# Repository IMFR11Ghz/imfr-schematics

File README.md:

# imfr-schematics
imfr-schematics

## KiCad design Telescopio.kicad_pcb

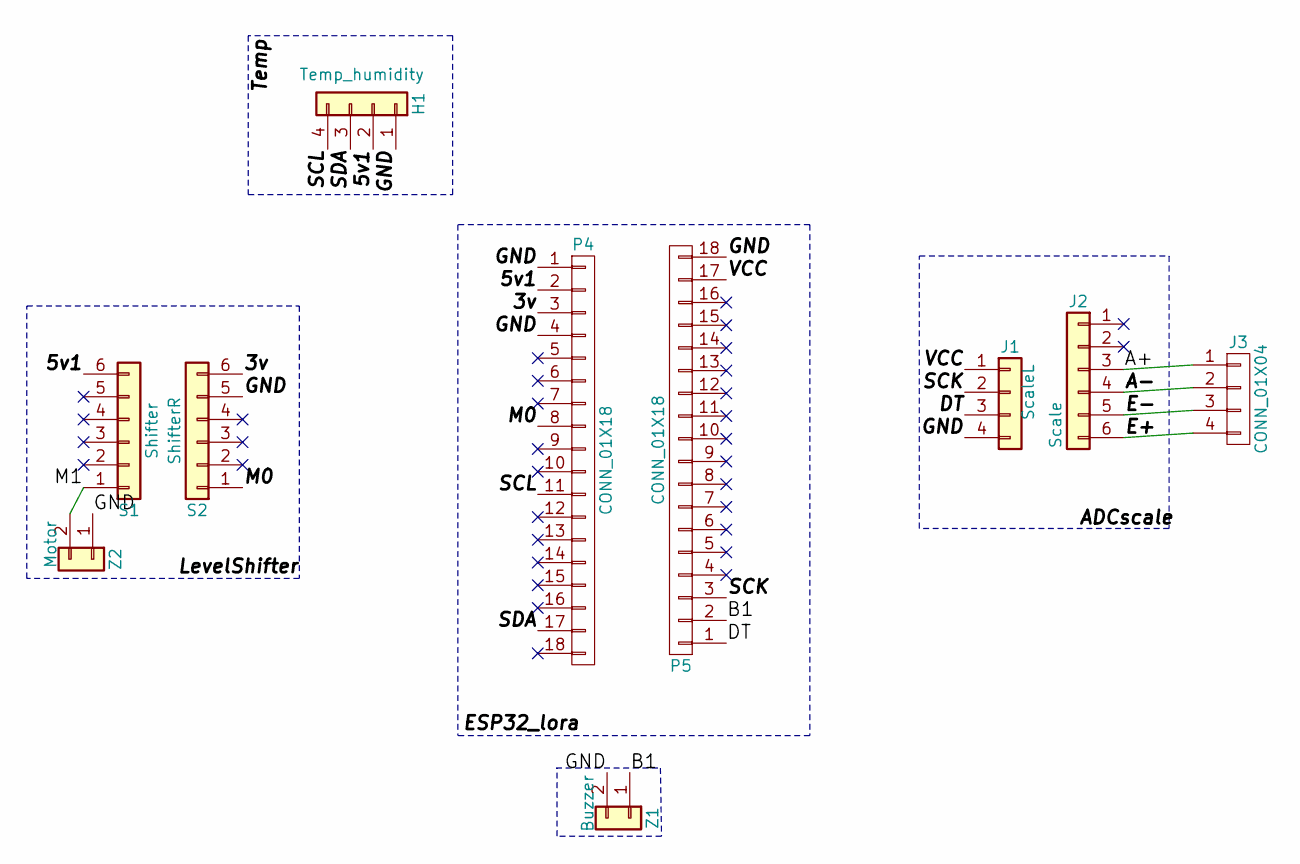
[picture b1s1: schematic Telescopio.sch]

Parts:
H1: Temp_humidity; Pin_Header_Straight_1x04_Pitch2.00mm
J1: ScaleL; Pin_Header_Straight_1x04
J2: Scale; Pin_Header_Straight_1x06
J3: CONN_01X04; Pin_Header_Straight_1x04_Pitch2.00mm
P4, P5: CONN_01X18; Pin_Header_Straight_1x18
S1: Shifter; Pin_Header_Straight_1x06
S2: ShifterR; Pin_Header_Straight_1x06
Z1: Buzzer; Pin_Header_Straight_1x02
Z2: Motor; Pin_Header_Straight_1x02

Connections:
/3v: P4.3, S2.6
/5v1: H1.2, P4.2, S1.6
/A+: J2.3, J3.1
/A-: J2.4, J3.2
/B1: P5.2, Z1.1
/DT: J1.3, P5.1
/E+: J2.6, J3.4
/E-: J2.5, J3.3
/GND: H1.1, J1.4, P4.1, P4.4, P5.18, S2.5, Z1.2, Z2.1
/M0: P4.8, S2.1
/M1: S1.1, Z2.2
/SCK: J1.2, P5.3
/SCL: H1.4, P4.11
/SDA: H1.3, P4.17
/VCC: J1.1, P5.17

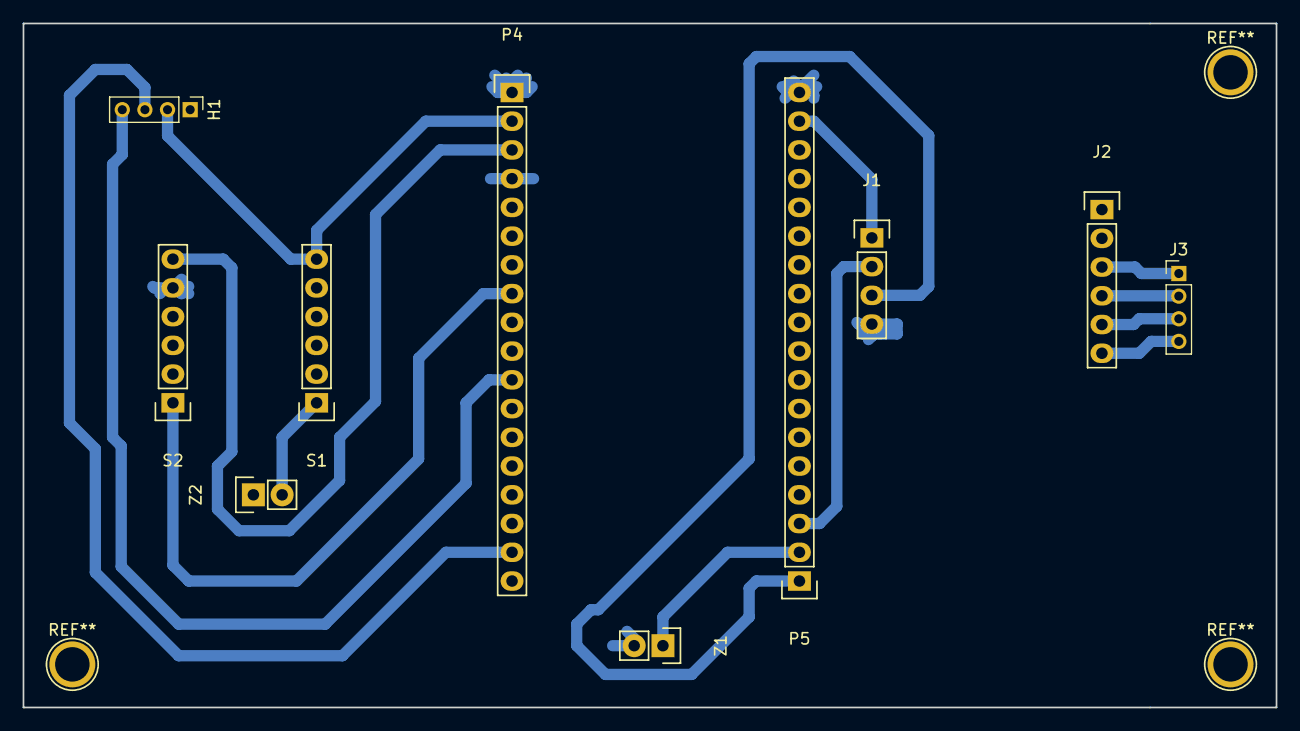
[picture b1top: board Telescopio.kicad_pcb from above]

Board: 2 copper layers, 110.7 x 60.5 mm, 10 parts (0 on the bottom side), 15 nets.

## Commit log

2017-06-16 initial commit repo Kicad
2017-06-16 print board
2017-06-16 eeschema image
2017-06-17 button reset
2017-07-04 gerber svg and dxf
2018-01-11 modifed pcb for testing
2018-01-11 mossing pbc file
2018-01-11 change label name
2018-01-11 general fixes
2018-01-11 added scale out
2018-03-02 add pinheaders 2.0mm
2018-03-02 add gerber and svg files
